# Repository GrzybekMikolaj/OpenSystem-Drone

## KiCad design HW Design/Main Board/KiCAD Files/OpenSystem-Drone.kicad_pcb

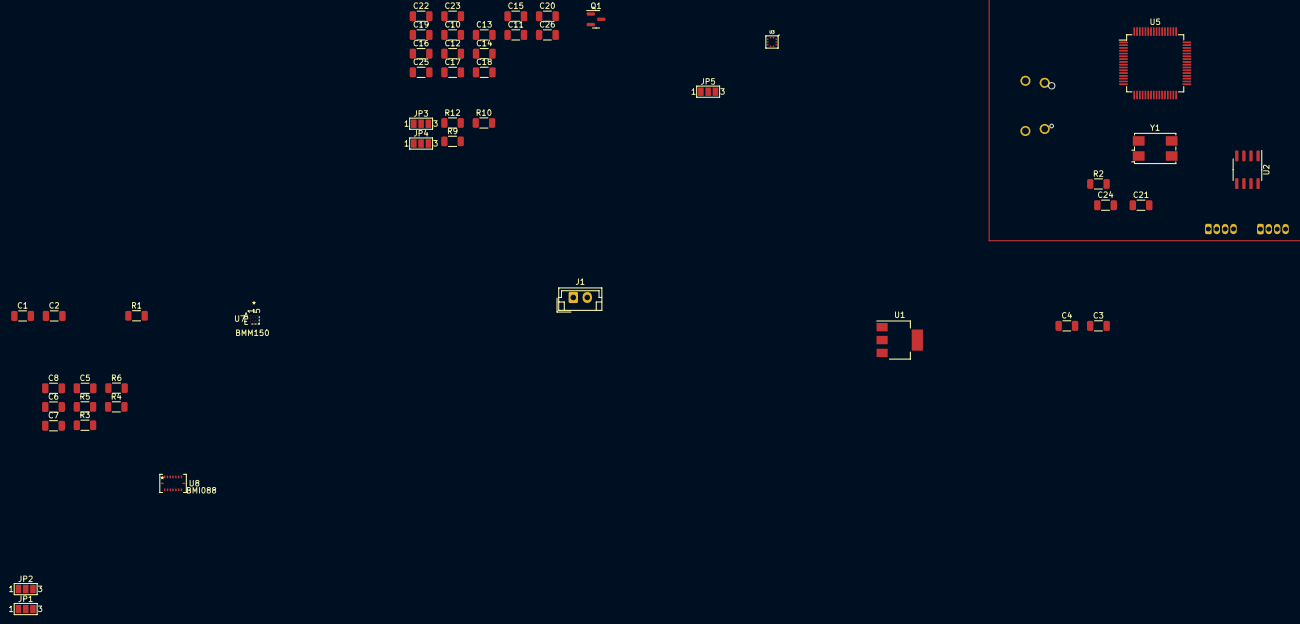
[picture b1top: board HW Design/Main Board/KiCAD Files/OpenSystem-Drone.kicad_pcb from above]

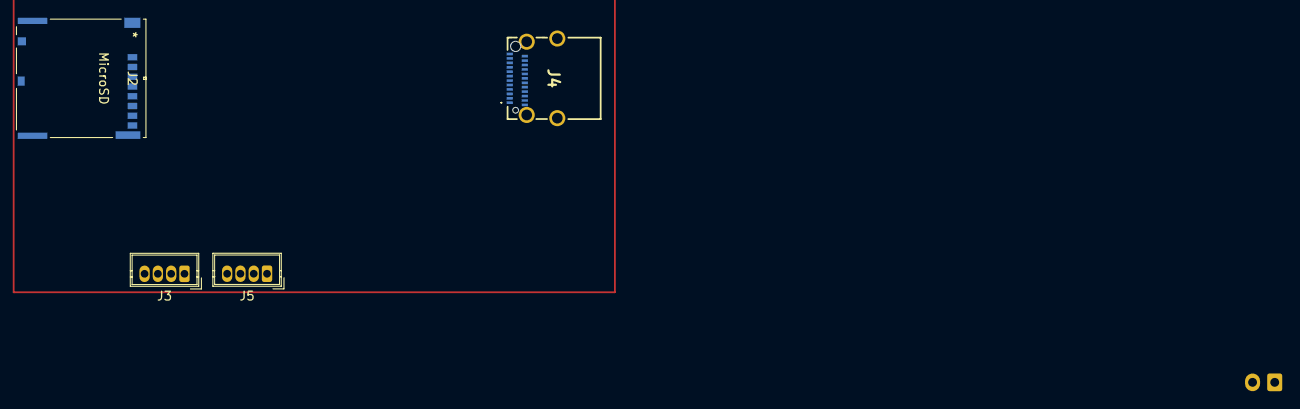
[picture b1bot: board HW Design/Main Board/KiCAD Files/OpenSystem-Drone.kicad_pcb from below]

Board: 2 copper layers, 52 parts (4 on the bottom side), 31 nets, no tracks yet.

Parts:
C1: 0.47 uF; C_1206_3216Metric
C2: 33uF; C_1206_3216Metric
C3, C5, C7: 100nF; C_1206_3216Metric
C4: 1uF; C_1206_3216Metric
C6: 10uF; C_1206_3216Metric
C8: C; C_1206_3216Metric
C10: 4u7; C_1206_3216Metric
C11, C13, C15, C16, C17, C18, C19, C20, C22, C23, C25, C26: 100n; C_1206_3216Metric
C12: 1u; C_1206_3216Metric
C14: 10n; C_1206_3216Metric
C21, C24: 12p; C_1206_3216Metric
J1: Conn_01x02_Female; JST_EH_B2B-EH-A_1x02_P2.50mm_Vertical
J2: MicroSD
J3, J5: CAN_1; Wuerth_WR-WTB_64800411622_1x04_P1.50mm_Vertical
J4: USB C; usb_c_amphenol
JP1, JP2, JP3, JP4, JP5: SolderJumper_3_Bridged12; SolderJumper-3_P1.3mm_Open_Pad1.0x1.5mm_NumberLabels
Q1: AO3401A; SOT-23
R1, R2: 0; R_1206_3216Metric
R3, R4, R6, R10, R12: 4k7; R_1206_3216Metric
R5, R9: R; R_1206_3216Metric
U1: LM3940IMP-3.3/NOPB; SOT-223
U2: SN65HVD232; SOIC-8_3.9x4.9mm_P1.27mm
U3: BMP581
U5: STM32F446RETx; LQFP-64_10x10mm_P0.5mm
U7: BMM150
U8: BMI088
Y1: 16MHZ; Crystal_SMD_7050-4Pin_7.0x5.0mm

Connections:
+3.3VA: C12.1, C14.1, U5.13 (VDDA)
+3V3: C2.1, C5.1, C6.1, C7.1, C8.1, C10.1, C11.1, C13.1, C15.1, C16.1, C17.1, C18.1, C19.1, C20.1, C22.1, C23.1, C25.1, C26.1, J2.4 (VDD), R3.1, R4.1, R5.1, R6.1, R9.1, R10.2, R12.1, U1.3 (OUT), U2.3 (VCC), U3.1 (VDDIO), U3.6 (CSB), U3.10 (VDD), U5.1 (VBAT), U5.19 (VDD), U5.32 (VDD), U5.48 (VDD), U5.64 (VDD), U7.A1 (PS), U7.B2 (VDDIO), U7.E5 (VDD), U8.3 (VDD), U8.7 (PS), U8.11 (VDDIO), U8.14 (CSB1)
+5V: C1.1, J1.2, J3.1, J5.1, U1.1 (IN)
ACC_AD: JP1.2 (C), U8.15 (SDO1)
CAN1_RX: U2.4 (R), U5.8 (PC0)
CAN1_TX: U2.1 (D), U5.9 (PC1)
CAN_1_H: J3.2, J5.2, U2.7 (CANH)
CAN_1_L: J3.3, J5.3, U2.6 (CANL)
GND: C1.2, C2.2, C3.2, C4.2, C5.2, C6.2, C7.2, C8.2, C10.2, C11.2, C12.2, C13.2, C14.2, C15.2, C16.2, C17.2, C18.2, C19.2, C20.2, C21.2, C22.2, C23.2, C24.2, C25.2, C26.2, J1.1, J2.6 (VSS), J2.11 (CASE), J2.12 (CASE), J2.13 (CASE), J2.14 (CASE), J3.4, J5.4, JP1.1 (A), JP2.1 (A), JP3.1 (A), JP4.1 (A), JP5.1 (A), Q1.1 (G), U1.2 (GND), U1.4 (GND), U2.2 (GND), U3.3 (GND), U3.8 (GND), U3.9 (GND), U5.12 (VSSA), U5.18 (VSS), U5.31 (VSS), U5.47 (VSS), U5.63 (VSS), U7.C5 (GND), U7.E1 (GND), U7.E3 (GND), U8.4 (GNDA), U8.6 (GNDIO), Y1.2, Y1.4
GYR_AD: JP2.2 (C), U8.10 (SDO2)
HSE_IN: C21.1, U5.5 (PH0), Y1.1
HSE_OUT: R2.2, U5.6 (PH1)
I2C1_SCL: R5.2, U3.2 (SCK/SCL), U5.58 (PB6), U7.A3 (SCK), U8.8 (SCL/SCK)
I2C1_SDA: R9.2, U3.4 (SDI/SDA), U5.59 (PB7), U7.B4 (SDI), U8.9 (SDA/SDI)
MAG_AD1: JP3.2 (C), U7.C1 (SDO)
MAG_AD2: JP4.2 (C), U7.A5 (CSB)
unnamed: C3.1, C4.1
unnamed: JP3.3 (B), R10.1
unnamed: JP4.3 (B), R12.2
unnamed: JP5.3 (B), R3.2
unnamed: C24.1, R2.1, Y1.3
unnamed: JP1.3 (B), R4.2
unnamed: JP2.3 (B), R6.2
PRS_AD: JP5.2 (C), U3.5 (SDO/ADR)
SPI1_SD_CLK: J2.5 (CLK), U5.21 (PA5)
SPI1_SD_CS: J2.2 (CD/DAT3), U5.20 (PA4)
SPI1_SD_MISO: J2.7 (DAT0), U5.22 (PA6)
SPI1_SD_MOSI: J2.3 (CMD), U5.23 (PA7)
USB_D+: J4.A6 (D+_1), U5.45 (PA12)
USB_D-: J4.A7 (D-_1), U5.44 (PA11)
xxx: U8.1 (INT2), U8.12 (INT3), U8.13 (INT4), U8.16 (INT1)

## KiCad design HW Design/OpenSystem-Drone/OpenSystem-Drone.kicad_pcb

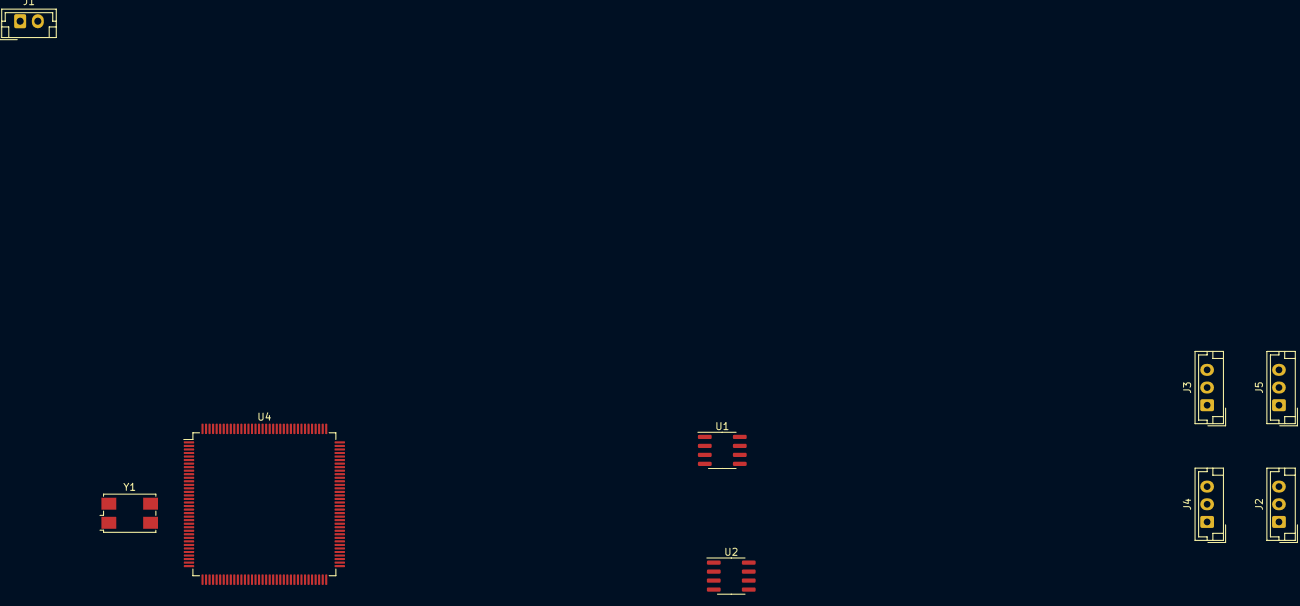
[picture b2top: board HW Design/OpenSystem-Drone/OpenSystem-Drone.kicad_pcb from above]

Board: 2 copper layers, 9 parts (0 on the bottom side), 12 nets, no tracks yet.

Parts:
J1: Conn_01x02_Female; JST_EH_B2B-EH-A_1x02_P2.50mm_Vertical
J2, J4: CAN_1; JST_EH_B3B-EH-A_1x03_P2.50mm_Vertical
J3, J5: CAN_2; JST_EH_B3B-EH-A_1x03_P2.50mm_Vertical
U1, U2: MCP2551-I-SN; SOIC-8_3.9x4.9mm_P1.27mm
U4: STM32F446ZETx; LQFP-144_20x20mm_P0.5mm
Y1: Crystal_GND2; Crystal_SMD_7050-4Pin_7.0x5.0mm

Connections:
+5V: J1.2, U1.3 (VDD), U2.3 (VDD)
CAN1_RX: U1.4 (RXD), U4.103 (PA11)
CAN1_TX: U1.1 (TXD), U4.104 (PA12)
CAN2_RX: U2.4 (RXD), U4.73 (PB12)
CAN2_TX: U2.1 (TXD), U4.74 (PB13)
CAN_1_H: J2.1, J4.1, U1.7 (CANH)
CAN_1_L: J2.2, J4.2, U1.6 (CANL)
CAN_2_H: J3.1, J5.1, U2.7 (CANH)
CAN_2_L: J3.2, J5.2, U2.6 (CANL)
GND: J1.1, J2.3, J3.3, J4.3, J5.3, U1.2 (VSS), U2.2 (VSS), U4.16 (VSS), U4.31 (VSSA), U4.38 (VSS), U4.51 (VSS), U4.61 (VSS), U4.83 (VSS), U4.94 (VSS), U4.107 (VSS), U4.120 (VSS), U4.130 (VSS), Y1.2, Y1.4
RCC_OSC_IN: U4.23 (PH0), Y1.3
RCC_OSC_OUT: U4.24 (PH1), Y1.1

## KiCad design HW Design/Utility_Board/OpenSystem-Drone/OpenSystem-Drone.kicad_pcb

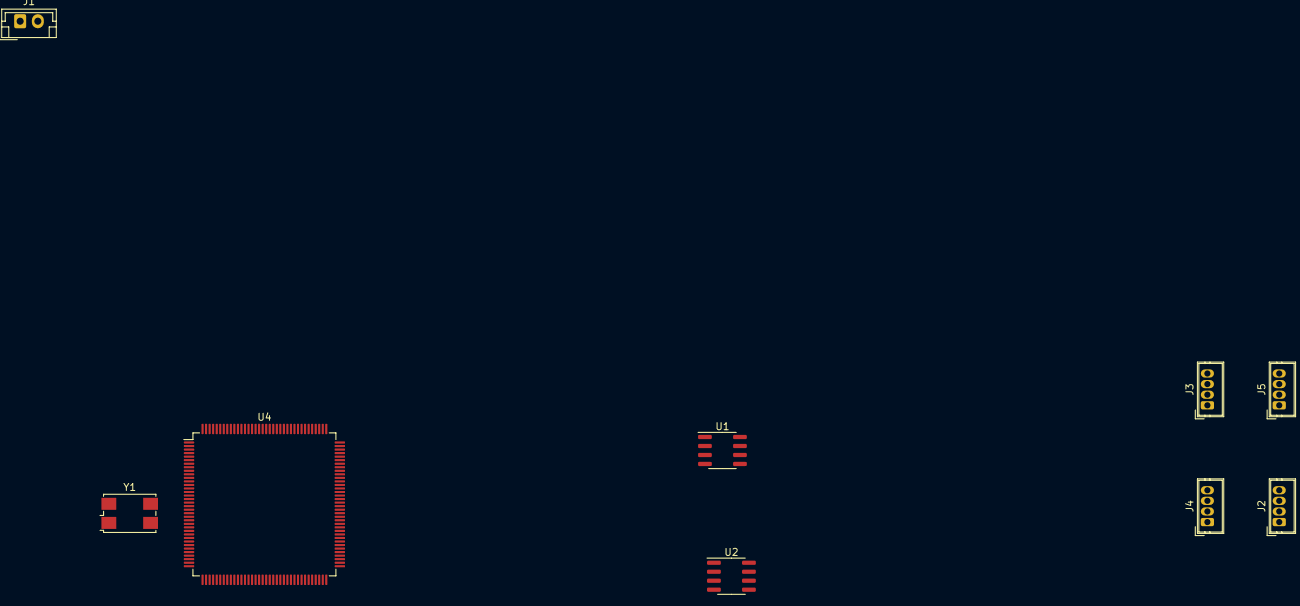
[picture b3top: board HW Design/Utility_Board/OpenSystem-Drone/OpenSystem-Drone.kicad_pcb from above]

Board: 2 copper layers, 9 parts (0 on the bottom side), 10 nets, no tracks yet.

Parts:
J1: Conn_01x02_Female; JST_EH_B2B-EH-A_1x02_P2.50mm_Vertical
J2, J4: CAN_1; Wuerth_WR-WTB_64800411622_1x04_P1.50mm_Vertical
J3, J5: CAN_2; Wuerth_WR-WTB_64800411622_1x04_P1.50mm_Vertical
U1, U2: MCP2551-I-SN; SOIC-8_3.9x4.9mm_P1.27mm
U4: STM32F446ZETx; LQFP-144_20x20mm_P0.5mm
Y1: Crystal_GND2; Crystal_SMD_7050-4Pin_7.0x5.0mm

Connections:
+5V: J1.2, J2.1, J3.1, J4.1, J5.1, U1.3 (VDD), U2.3 (VDD)
CAN1_RX: U1.4 (RXD), U4.103 (PA11)
CAN1_TX: U1.1 (TXD), U4.104 (PA12)
CAN2_RX: U2.4 (RXD), U4.73 (PB12)
CAN2_TX: U2.1 (TXD), U4.74 (PB13)
CAN_1_H: J2.2, J4.2, U1.7 (CANH)
CAN_1_L: J2.3, J4.3, U1.6 (CANL)
CAN_2_H: J3.2, J5.2, U2.7 (CANH)
CAN_2_L: J3.3, J5.3, U2.6 (CANL)
GND: J1.1, J2.4, J3.4, J4.4, J5.4, U1.2 (VSS), U2.2 (VSS), U4.16 (VSS), U4.31 (VSSA), U4.38 (VSS), U4.51 (VSS), U4.61 (VSS), U4.83 (VSS), U4.94 (VSS), U4.107 (VSS), U4.120 (VSS), U4.130 (VSS), Y1.2, Y1.4

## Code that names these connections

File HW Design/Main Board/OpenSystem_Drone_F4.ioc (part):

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Mcu.Name=STM32F446Z(C-E)Tx
Mcu.Package=LQFP144
Mcu.UserName=STM32F446ZETx
PA11.Mode=Device_Only
PA11.Signal=USB_OTG_FS_DM
PA12.Mode=Device_Only
PA12.Signal=USB_OTG_FS_DP
PA13.Mode=Trace_Asynchronous_SW
PA13.Signal=SYS_JTMS-SWDIO
PA14.Mode=Trace_Asynchronous_SW
PA14.Signal=SYS_JTCK-SWCLK
PA4.GPIOParameters=GPIO_Label
PA4.GPIO_Label=SPI1_SD_CS
PA4.Signal=GPIO_Output
PA5.GPIOParameters=GPIO_Label
PA5.GPIO_Label=SPI1_SD_CLK
PA5.Mode=Full_Duplex_Master
PA5.Signal=SPI1_SCK
PA6.GPIOParameters=GPIO_Label
PA6.GPIO_Label=SPI1_SD_MISO
PA6.Mode=Full_Duplex_Master
PA6.Signal=SPI1_MISO
PA7.GPIOParameters=GPIO_Label
PA7.GPIO_Label=SPI1_SD_MOSI
PA7.Mode=Full_Duplex_Master
PA7.Signal=SPI1_MOSI
PB3.Mode=Trace_Asynchronous_SW
PB3.Signal=SYS_JTDO-SWO
PB6.GPIOParameters=GPIO_Label
PB6.GPIO_Label=I2C1_SCL
PB6.Mode=I2C
PB6.Signal=I2C1_SCL
PB7.GPIOParameters=GPIO_Label
PB7.GPIO_Label=I2C1_SDA
PB7.Mode=I2C
PB7.Signal=I2C1_SDA
PC6.Mode=Asynchronous
PC6.Signal=USART6_TX
PC7.Mode=Asynchronous
PC7.Signal=USART6_RX
PD0.Mode=CAN_Activate
PD0.Signal=CAN1_RX
PD1.Mode=CAN_Activate
PD1.Signal=CAN1_TX
PH0-OSC_IN.Mode=HSE-External-Oscillator
PH0-OSC_IN.Signal=RCC_OSC_IN
PH1-OSC_OUT.Mode=HSE-External-Oscillator
PH1-OSC_OUT.Signal=RCC_OSC_OUT
board=custom

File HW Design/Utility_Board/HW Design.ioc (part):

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Mcu.Name=STM32F446Z(C-E)Tx
Mcu.Package=LQFP144
Mcu.UserName=STM32F446ZETx
PA11.Mode=CAN_Activate
PA11.Signal=CAN1_RX
PA12.Mode=CAN_Activate
PA12.Signal=CAN1_TX
PB12.Mode=CAN_Activate
PB12.Signal=CAN2_RX
PB13.Mode=CAN_Activate
PB13.Signal=CAN2_TX
PH0-OSC_IN.Signal=RCC_OSC_IN
PH1-OSC_OUT.Signal=RCC_OSC_OUT
board=custom

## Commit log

2023-03-16 Stakeholder Requirements - first commit
2023-03-19 hw design init
2023-03-19 Added draft .ioc for F1
2023-03-26 hw desgign updates
2023-04-18 Updates of HW Desgin

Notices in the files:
parts and their libraries:
Copyright 2021 Accelerated Designs. All rights reserved.
